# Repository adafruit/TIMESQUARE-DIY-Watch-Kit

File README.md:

# PCB for the Adafruit TIMESQUARE DIY Watch Kit 

<a href="http://www.adafruit.com/products/1106"><br/>Click here to purchase one from the Adafruit shop</a>

__Format is EagleCAD schematic and board layout__

Show up stylish AND on time to any event with this awesome looking DIY watch. We have a few watch kits here at Adafruit but we finally have one that looks good and fits well, even for ladies and kids and others with smaller wrists and hands. Its got an 8x8 bit matrix display and a repurposed silicone watch band for a professional look.

64 LEDs light up to tell you the time in a variety of ways. Built into the kit are 3 different watch 'faces' - a scrolling marquee with time and date, a binary watch display (for geeks, robots, and binary fans), and a moon phase display (for beach-combers, werewolves). There's also a built-in battery meter so you can check your battery life. [Want to make your own watch? Easy! The microcontroller is an Arduino-compatible, all you need is an FTDI Friend and the Arduino IDE and you can design your own watch faces and upload them to the TIMESQUARE.](http://learn.adafruit.com/timesquare-watch-kit/uploading-new-firmware)

Engineered for greatness by PaintYourDragon, this watch squeezes 500-1000 full time displays out of a coin battery, and up to one year 'resting' lifetime, so you can use this as a day-to-day timekeeper.

This watch comes with an ultra bright red LED matrix and a black silicone watch band that fits all wrists from children to adult.

The band is an "off-the-shelf" band that holds the watch in pretty well, we'll be creating other bands - the included band is to just get you started! This watch is meant to be hackable, from the software to the band!

This is a DIY kit, and requires some basic soldering/assembly to put together. It is a beginner kit, so this is a fine project to use in learning how to solder. Tools are not included, you'll need a soldering iron, solder and diagonal cutters as a minimum. [Check the tutorial page for details on what tools and steps are required to assemble.](http://learn.adafruit.com/timesquare-watch-kit). Take about 1-2 hours to put together. Build it in the afternoon and you'll be done in time to hit the clubs in the evening.

[For more information and downloads check out the page in the Adafruit Learning System.](http://learn.adafruit.com/timesquare-watch-kit)

## License
Adafruit invests time and resources providing this open source design,
please support Adafruit and open-source hardware by purchasing
products from Adafruit!

Designed by Adafruit Industries.
Creative Commons Attribution, Share-Alike license, check license.txt for more information
All text above must be included in any redistribution

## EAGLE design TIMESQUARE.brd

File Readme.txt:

This is the PCB for the Adafruit TIMESQUARE DIY Watch Kit
Format is EagleCAD schematic and board layout

For more details, check out the product page at

-----> http://www.adafruit.com/products/1106

Adafruit invests time and resources providing this open source design, 
please support Adafruit and open-source hardware by purchasing 
products from Adafruit!

Designed by Adafruit Industries.  
Creative Commons Attribution, Share-Alike license, check license.txt for more information
All text above must be included in any redistribution

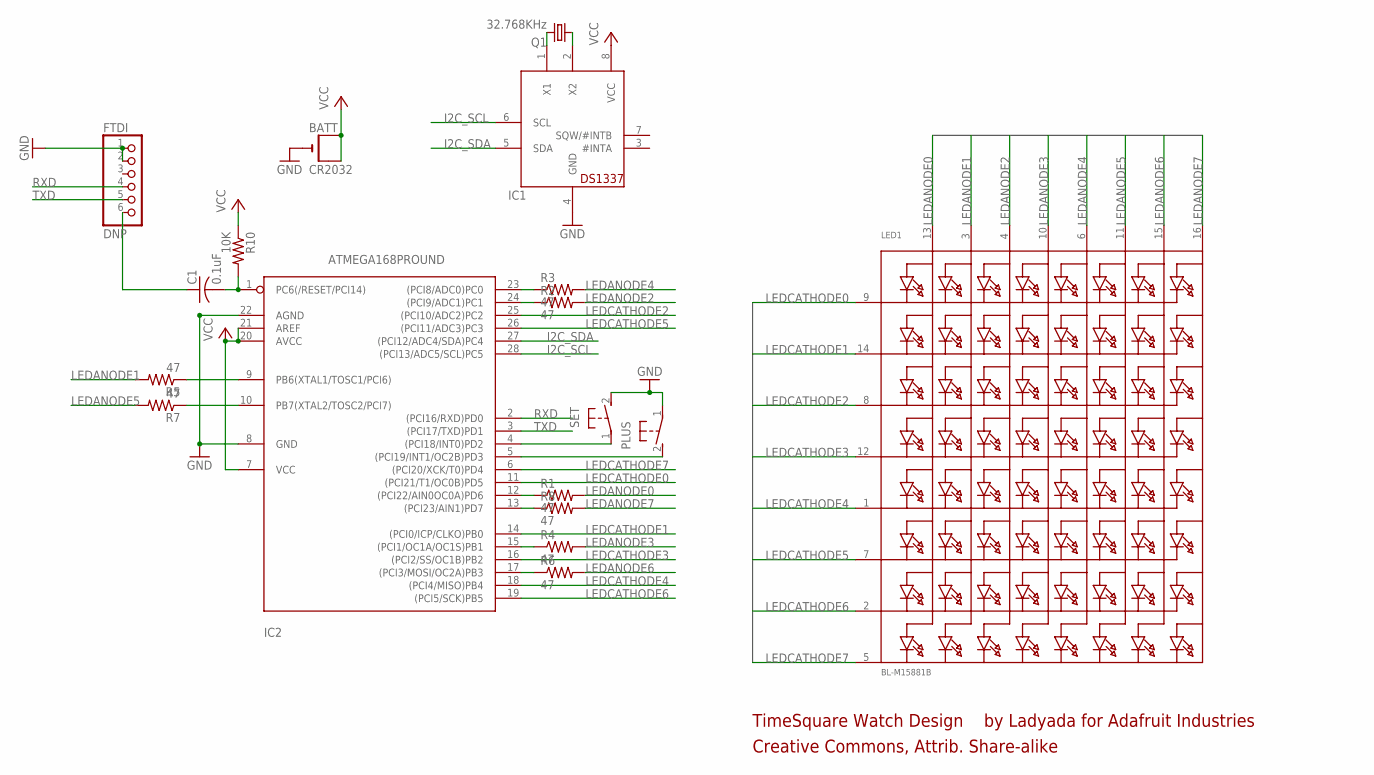
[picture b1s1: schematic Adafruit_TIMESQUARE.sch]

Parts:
BATT: CR2032; CR2032-THRU
C1: 0.1uF; C025-025X050
FTDI: DNP; 1X06-CLEAN
IC1: DS1337; DIL08-ROUND
IC2: ATMEGA168PROUND; DIL28-3-ROUND
LED1: BL-M15881B; SEGMENT_BL-M15A881
PLUS: 31-XXSKINNY; B3F-31XX-SKINNIER
Q1: 32.768KHz; TC38H
R1, R2, R3, R4, R5, R6, R7, R8: 47; 0204/7
R10: 10K; 0204/7
SET: 31-XXSKINNY; B3F-31XX-SKINNIER

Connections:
GND: BATT.-, FTDI.1, FTDI.2, IC1.4 (GND), IC2.8 (GND), IC2.22 (AGND), PLUS.1, SET.2 (S)
I2C_SCL: IC1.6 (SCL), IC2.28 ((PCI13/ADC5/SCL)PC5)
I2C_SDA: IC1.5 (SDA), IC2.27 ((PCI12/ADC4/SDA)PC4)
LEDANODE0: LED1.13 (A1), R1.2
LEDANODE1: LED1.3 (A2), R5.2
LEDANODE2: LED1.4 (A3), R2.2
LEDANODE3: LED1.10 (A4), R4.2
LEDANODE4: LED1.6 (A5), R3.2
LEDANODE5: LED1.11 (A6), R7.2
LEDANODE6: LED1.15 (A7), R6.2
LEDANODE7: LED1.16 (A8), R8.2
LEDCATHODE0: IC2.11 ((PCI21/T1/OC0B)PD5), LED1.9 (K1)
LEDCATHODE1: IC2.14 ((PCI0/ICP/CLKO)PB0), LED1.14 (K2)
LEDCATHODE2: IC2.25 ((PCI10/ADC2)PC2), LED1.8 (K3)
LEDCATHODE3: IC2.16 ((PCI2/SS/OC1B)PB2), LED1.12 (K4)
LEDCATHODE4: IC2.18 ((PCI4/MISO)PB4), LED1.1 (K5)
LEDCATHODE5: IC2.26 ((PCI11/ADC3)PC3), LED1.7 (K6)
LEDCATHODE6: IC2.19 ((PCI5/SCK)PB5), LED1.2 (K7)
LEDCATHODE7: IC2.6 ((PCI20/XCK/T0)PD4), LED1.5 (K8)
unnamed: C1.2, IC2.1 (PC6(/RESET/PCI14)), R10.2
unnamed: IC1.1 (X1), Q1.2
unnamed: IC1.2 (X2), Q1.1
unnamed: IC2.4 ((PCI18/INT0)PD2), SET.1
unnamed: IC2.5 ((PCI19/INT1/OC2B)PD3), PLUS.2 (S)
unnamed: IC2.12 ((PCI22/AIN0OC0A)PD6), R1.1
unnamed: IC2.23 ((PCI8/ADC0)PC0), R3.1
unnamed: IC2.9 (PB6(XTAL1/TOSC1/PCI6)), R5.1
unnamed: IC2.10 (PB7(XTAL2/TOSC2/PCI7)), R7.1
unnamed: IC2.24 ((PCI9/ADC1)PC1), R2.1
unnamed: IC2.17 ((PCI3/MOSI/OC2A)PB3), R6.1
unnamed: IC2.13 ((PCI23/AIN1)PD7), R8.1
unnamed: IC2.15 ((PCI1/OC1A/OC1S)PB1), R4.1
unnamed: C1.1, FTDI.6
RXD: FTDI.4, IC2.2 ((PCI16/RXD)PD0)
TXD: FTDI.5, IC2.3 ((PCI17/TXD)PD1)
VCC: BATT.+1 (+), BATT.+2 (+1), IC1.8 (VCC), IC2.7 (VCC), IC2.20 (AVCC), IC2.21 (AREF), R10.1

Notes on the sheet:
TimeSquare Watch Design
by Ladyada for Adafruit Industries
Creative Commons, Attrib. Share-alike

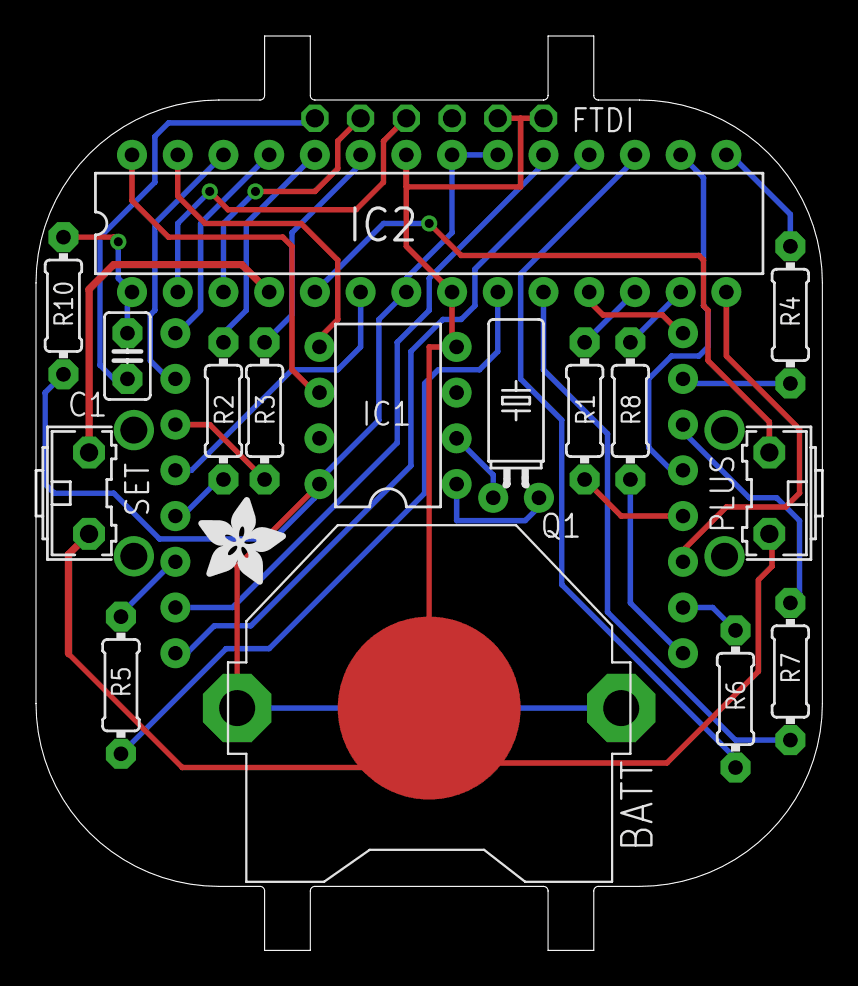
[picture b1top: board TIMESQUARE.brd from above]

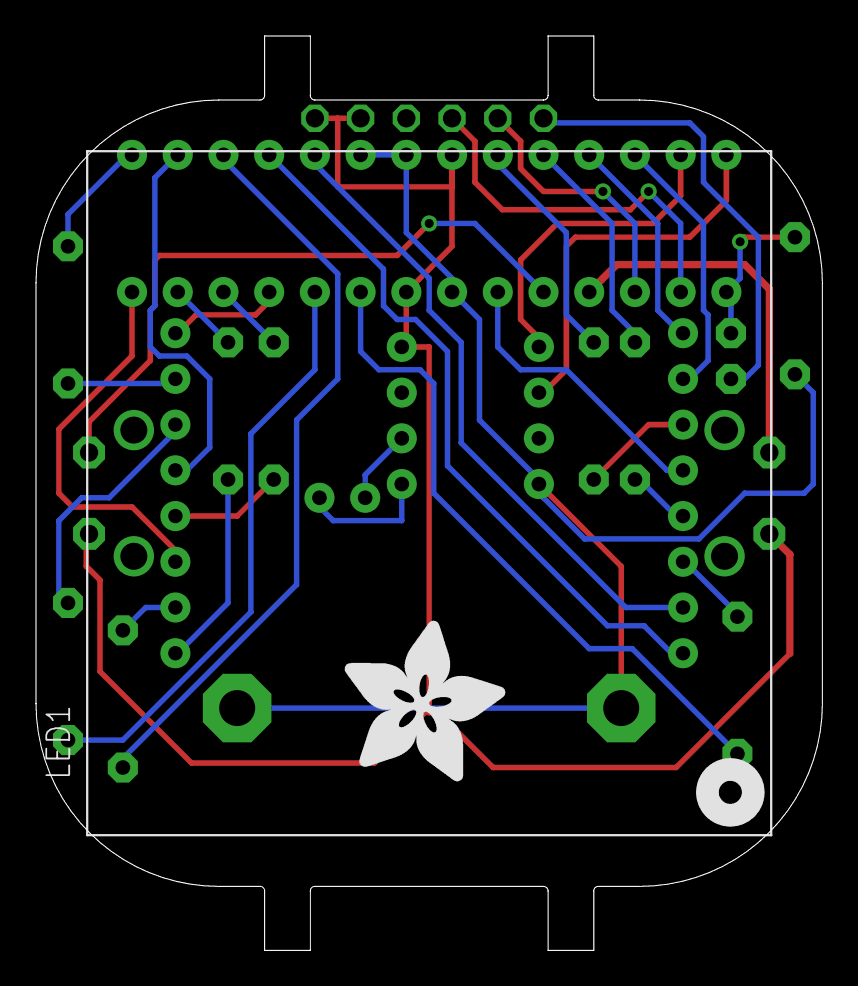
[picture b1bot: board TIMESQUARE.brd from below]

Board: 2 copper layers, 43.7 x 50.8 mm, 20 parts (2 on the bottom side), 36 nets.

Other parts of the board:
U$1: ADAFRUIT_5MM
U$2: ADAFRUIT_9MM

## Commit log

2013-01-13 Eagle files!
2013-01-13 read me
2019-04-18 new readme + image
2019-04-18 readded license

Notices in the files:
parts and their libraries:
microbuilder: This work is placed in the public domain, and may be freely used for commercial and non-commercial work with the following conditions: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
